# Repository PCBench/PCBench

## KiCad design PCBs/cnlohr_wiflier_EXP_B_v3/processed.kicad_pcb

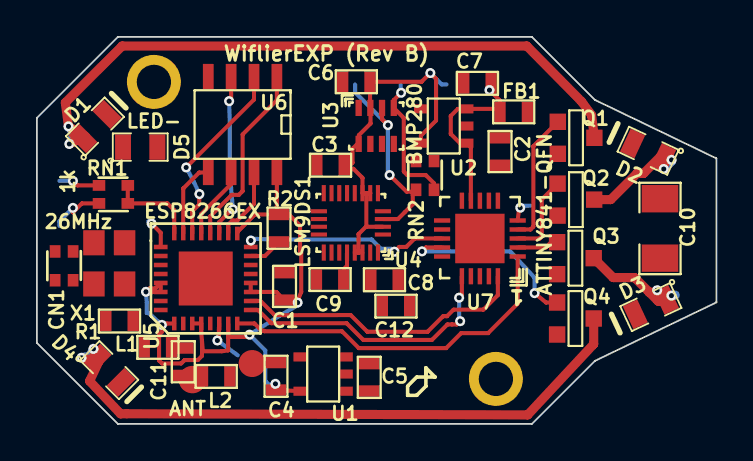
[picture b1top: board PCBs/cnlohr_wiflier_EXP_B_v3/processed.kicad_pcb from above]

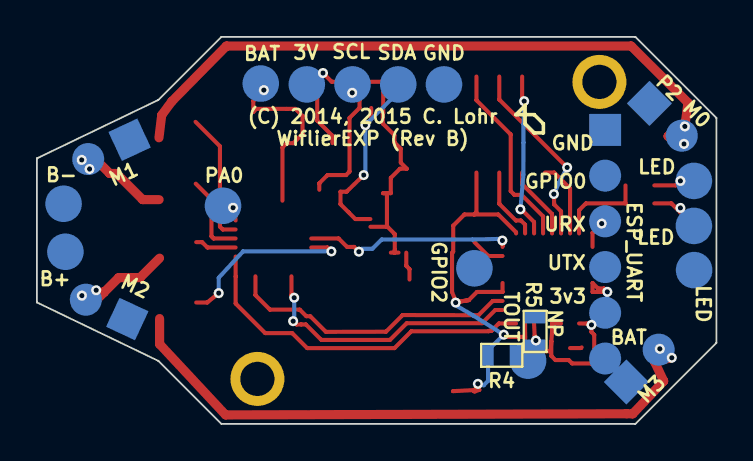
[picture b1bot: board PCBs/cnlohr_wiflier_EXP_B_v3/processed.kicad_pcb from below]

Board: 2 copper layers, 37.8 x 21.5 mm, 61 parts (20 on the bottom side), 28 nets.

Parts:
C1, C2, C3, C5: 10uF; SM0603
C4: 1uF; SM0603
C6, C8, C12: .1u; SM0603
C7: .1uF; SM0603
C9: 10nF; SM0603
C10: 100uF; SM1206
C11: 5.6pF; SM0603
CN1: 10p; NETWORK0606
D1, D2, D3, D4: 20V_500mA; SM0805
D5: LED-; SM0805
FB1: -; SM0603
L1, L2: NP; SM0603
P1: GPIO2; .1SMTPIN
P2: M0; SMT_1x2
P3: M1; SMT_1x2
P4: M2; SMT_1x2
P5: M3; SMT_1x2
P6, P19: ANT; .1SMTPIN
P7, P8: HOLE-1.9MM
P9: SDA; .1SMTPIN
P10: SCL; .1SMTPIN
P11: 3V; .1SMTPIN
P12: GND; .1SMTPIN
P13, P14, P15: LED; .1SMTPIN
P16: BAT; .1SMTPIN
P17: TOUT; .1SMTPIN
P18: PA0; .1SMTPIN
P21: B+; .1SMTPIN
P24: B-; .1SMTPIN
P32: ESP_UART; SMT_1x6
Q1, Q2, Q3, Q4: 7A_20V; SOT23GDS
R1, R2, R4: 12k; SM0603
R5: NP; SM0603
RN1, RN2: 1k; NETWORK0606
U1: MCP1824/3.3; SOT23-5
U2: MCP1824/3.0; SOT23-5
U3: BMP280
U4: LSM9DS1; LGA-24B
U5: ESP8266EX; QFN32
U6: W25Q16DV; SO8E
U7: ATTINY841-QFN; QFN20
X1: 26MHz; XTAL4P

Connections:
+3.3V: C1.1, R2.2, R4.1, U1.5, U5.1, U5.3, U5.4, U5.7, U5.11, U5.12, U5.17, U5.29, U5.30, U6.8
+3.3VP: C6.1, P11.1, U2.5, U4.3, U4.7, U4.8, U4.22, U4.23
AVRMISO: U5.10, U7.20
AVRMOSI: U5.9, U7.16
AVRRST: U5.16, U7.13
AVRSCK: U5.8, U7.1
GP5: RN1.1, RN1.3, U5.24
GPIO0: R2.1, U5.15
MTR0: Q1.G, U7.4
MTR1: Q2.G, U7.3
MTR2: Q3.G, U7.2
MTR3: Q4.G, U7.14
unnamed: P18.1, U7.5
unnamed: P13.1, RN1.2
unnamed: C9.2, U4.21
unnamed: C11.1, L1.1
unnamed: P14.1, RN1.4
unnamed: U5.20, U6.1
unnamed: U5.21, U6.6
unnamed: U5.22, U6.2
unnamed: U5.23, U6.5
unnamed: U5.19, U6.3
unnamed: U5.18, U6.7
SCL: P10.1, RN2.3, U3.4
SDA: P9.1, U3.3, U4.4
TOUT: R4.2, U5.6
URX: P32.3, U5.25
VAA: FB1.1, P16.1, U2.1, U2.3, U7.9

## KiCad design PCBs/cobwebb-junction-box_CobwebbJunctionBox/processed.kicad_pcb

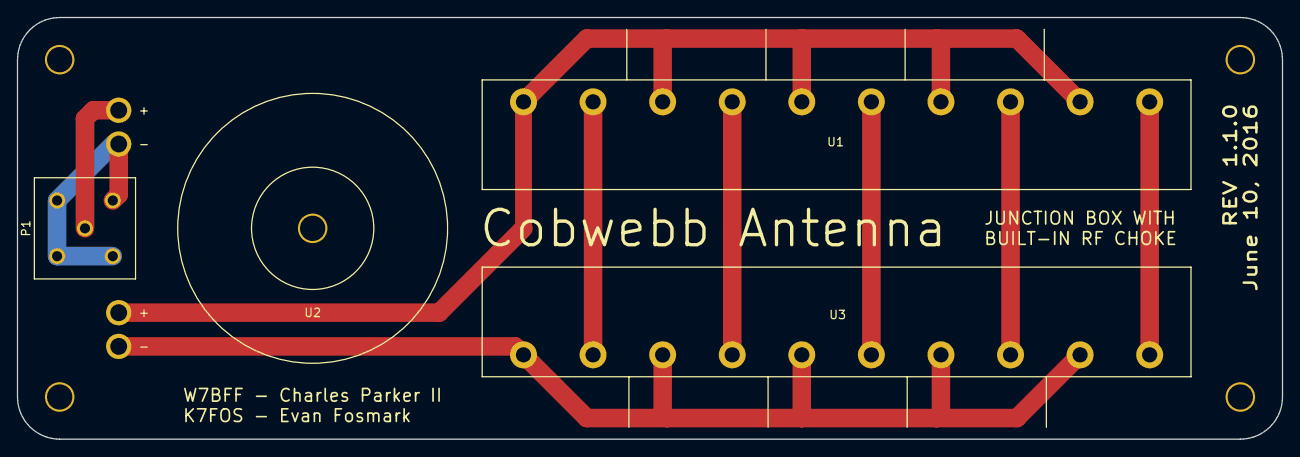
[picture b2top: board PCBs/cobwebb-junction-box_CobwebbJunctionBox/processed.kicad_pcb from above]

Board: 2 copper layers, 150.0 x 50.0 mm, 4 parts (0 on the bottom side), 9 nets.

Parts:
P1: BNC; BNC_Connector
U1, U3: Terminal_Block_10_Pin
U2: RF_Choke; RF_Choke_T106-2

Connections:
unnamed: P1.1, U2.2
unnamed: P1.2, U2.1
unnamed: U1.1, U3.10
unnamed: U1.3, U3.8
unnamed: U1.5, U3.6
unnamed: U1.7, U3.4
unnamed: U1.9, U3.2
unnamed: U1.2, U1.4, U1.6, U1.8, U1.10, U2.3
unnamed: U2.4, U3.1, U3.3, U3.5, U3.7, U3.9

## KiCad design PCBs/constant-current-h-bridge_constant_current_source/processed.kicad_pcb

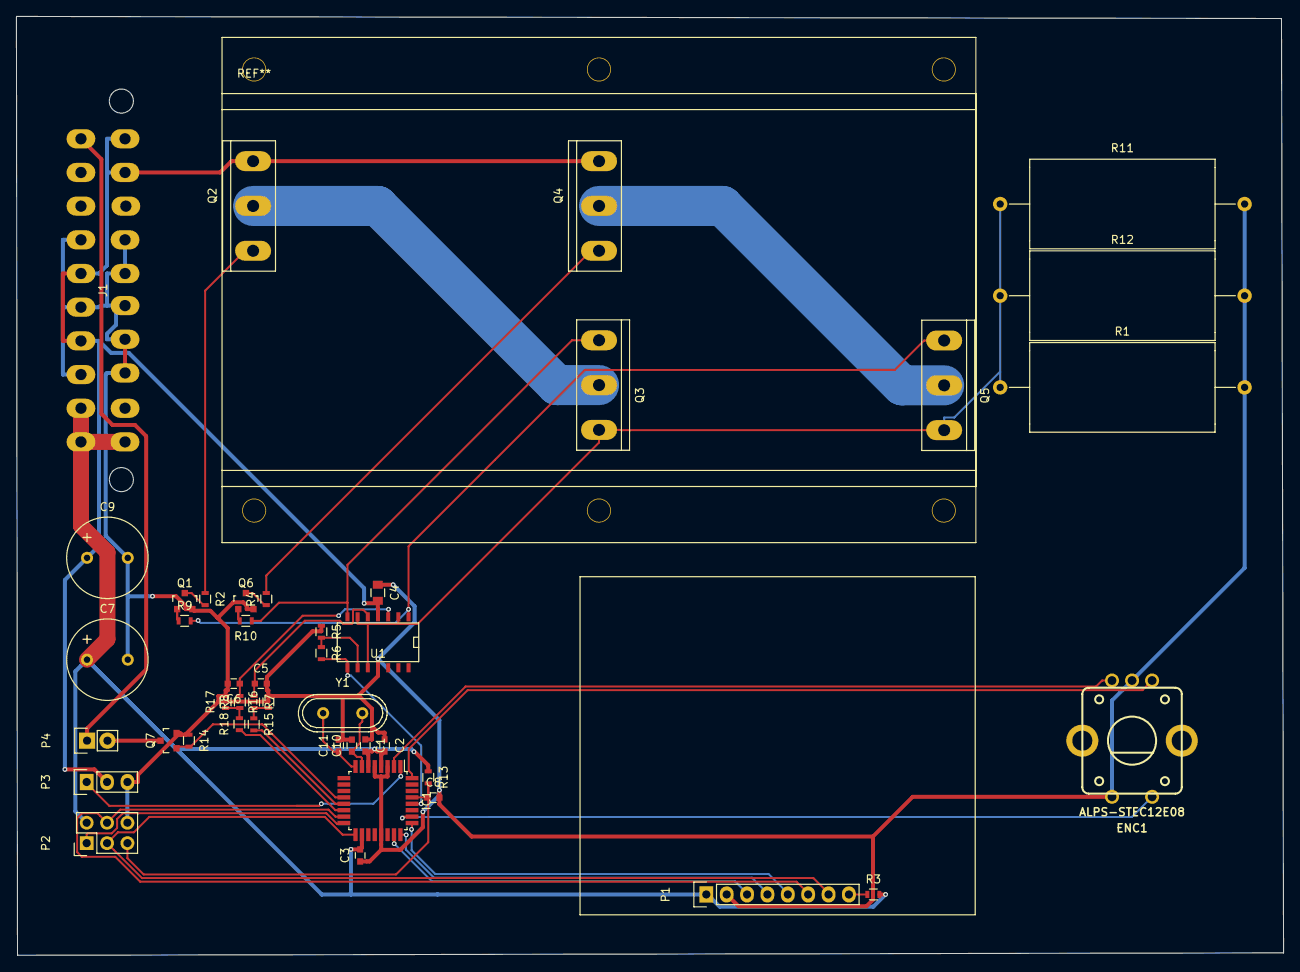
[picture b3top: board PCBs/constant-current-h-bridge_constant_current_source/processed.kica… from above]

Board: 2 copper layers, 158.0 x 117.1 mm, 45 parts (0 on the bottom side), 39 nets.

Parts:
C1, C2, C3: 100n; C_0603
C4: C; C_0805
C5, C6: 47n; C_0603
C7, C9: CP; Elko_vert_20x10mm_RM5
C8: C; C_0603
C10, C11: 22p; C_0603
ENC1: ALPS-STEC12E08
IC1: ATMEGA328P-A; TQFP-32_7x7mm_Pitch0.8mm
J1: ATX20; Molex_minifit_jr_5566_39-29-9203_20pin
P1: Nokia5110_Display
P2: CONN_02X03; Pin_Header_Straight_2x03
P3: CONN_01X03; Pin_Header_Straight_1x03
P4: CONN_01X02; Pin_Header_Straight_1x02
Q1, Q6: BC847; SOT-23
Q2, Q4: BD250; TO-247_Vertical_Neutral123
Q3, Q5: BD249; TO-247_Vertical_Neutral123
Q7: IRLML6244; SOT-23
R1, R11, R12: 0R1; Resistor_Ceramic_Horizontal_L23mm-W9mm-H9mm-p30mm
R2, R4: 1k5; R_0603
R3: 220; R_0603
R5, R9, R10, R14: 10k; R_0603
R6: 12k; R_0603
R7, R8: 100; R_0603
R13: R; R_0603
R15, R18: 180; R_0603
R16, R17: 150; R_0603
U1: LM324; SOIC-14_N
Y1: Crystal; Crystal_HC49-U_Vertical

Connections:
+3V3: C1.2, C2.2, C3.2, C7.1, IC1.4, IC1.6, IC1.18, J1.1, J1.2, J1.11, P1.1, P2.2, R3.2, R13.1
+5V: C4.2, C9.1, J1.4, J1.6, J1.19, J1.20, P3.2, Q2.3, Q4.3, U1.4
+12V: J1.10, P4.1
/MISO: IC1.16, P2.1
/MOSI: IC1.15, P1.6, P2.4
/RESET: C8.1, IC1.29, P2.5, R13.2
/SCK: IC1.17, P1.7, P2.3
/XTAL1: C10.1, IC1.7, Y1.2
/XTAL2: C11.1, IC1.8, Y1.1
/lcd_dc: IC1.25, P1.5
/lcd_rst: IC1.24, P1.4
/lcd_sce: IC1.23, P1.3
/load_1: Q2.2, Q3.2
/load_2: Q4.2, Q5.2
/mcu_adc: IC1.28, R6.2, U1.8
/mcu_airpump: IC1.12, Q7.1, R14.2
/opa_neg: Q5.1, R9.2, U1.1
/opa_pos: Q3.1, R10.1, U1.7
/pwm_neg: IC1.14, R18.1
/pwm_pos: IC1.13, R15.2
/rot_enc1: ENC1.A, IC1.32
/rot_enc2: ENC1.B, IC1.2
/rot_sw: ENC1.SW1, IC1.26
/servo_pwm: IC1.1, P3.1
GND: C1.1, C2.1, C3.1, C4.1, C5.2, C6.2, C7.2, C8.2, C9.2, C10.2, C11.2, ENC1.C, ENC1.SW2, IC1.3, IC1.5, IC1.21, J1.3, J1.5, J1.7, J1.13, J1.14, J1.15, J1.16, J1.17, P1.2, P2.6, P3.3, Q1.2, Q6.2, Q7.2, R1.2, R5.1, R11.2, R12.2, R14.1, R16.2, R17.2, U1.11
unnamed: C5.1, R7.1, U1.5
unnamed: C6.1, R8.2, U1.3
unnamed: P1.8, R3.1
unnamed: P4.2, Q7.3
unnamed: Q1.1, R9.1
unnamed: Q1.3, R2.2
unnamed: Q2.1, R2.1
unnamed: Q3.3, Q5.3, R1.1, R11.1, R12.1, U1.2, U1.6, U1.10
unnamed: Q4.1, R4.2
unnamed: Q6.1, R10.2
unnamed: Q6.3, R4.1
unnamed: R5.2, R6.1, U1.9
unnamed: R7.2, R15.1, R16.1
unnamed: R8.1, R17.1, R18.2

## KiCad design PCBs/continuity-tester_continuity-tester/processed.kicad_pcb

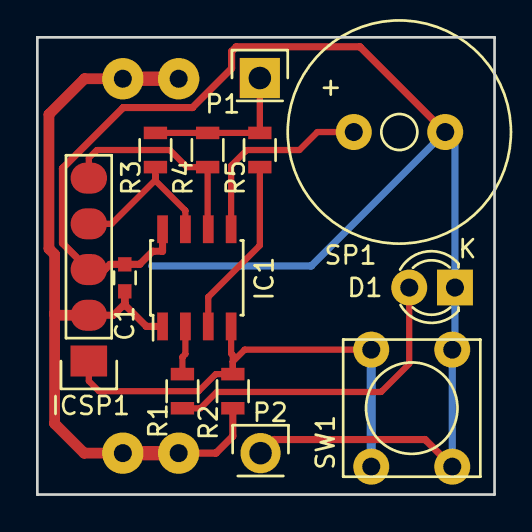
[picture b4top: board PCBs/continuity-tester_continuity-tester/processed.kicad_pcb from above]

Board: 2 copper layers, 25.4 x 25.4 mm, 14 parts (1 on the bottom side), 10 nets.

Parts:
BT1: CR2032; BAT-HLD-001-THM-OTL
C1: 100n; C_0603
D1: LED; LED-3MM
IC1: PIC12LF1571-I/SN; SOIC-8_3.9x4.9mm_Pitch1.27mm
ICSP1: CONN_01X05; Pin_Header_Straight_1x05
P1, P2: CONN_01X01; Pin_Header_Straight_1x01
R1: 4K7; R_0805
R2, R3, R4: 22k; R_0805
R5: 4k7; R_0805
SP1: SPEAKER; Buzzer_12x9.5RM7.6
SW1: SW_PUSH; SW_PUSH_SMALL

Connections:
unnamed: BT1.1, C1.1, IC1.1, ICSP1.2, R2.2
unnamed: BT1.2, C1.2, D1.1, IC1.8, ICSP1.3, P2.1, SP1.2, SW1.1
unnamed: D1.2, R1.1
unnamed: IC1.2, R1.2
unnamed: IC1.3, R5.2
unnamed: IC1.4, ICSP1.1, R2.1, SW1.2
unnamed: IC1.5, SP1.1
unnamed: IC1.6, ICSP1.5, R4.2
unnamed: IC1.7, ICSP1.4, R3.2
unnamed: P1.1, R3.1, R4.1, R5.1

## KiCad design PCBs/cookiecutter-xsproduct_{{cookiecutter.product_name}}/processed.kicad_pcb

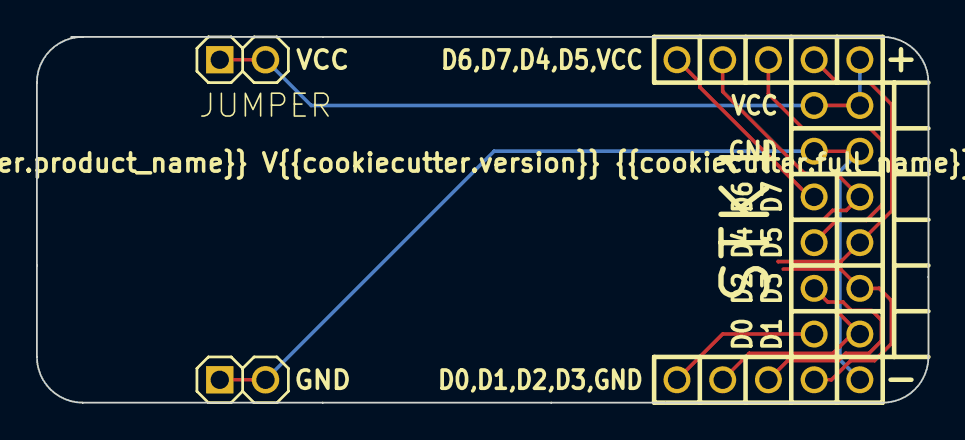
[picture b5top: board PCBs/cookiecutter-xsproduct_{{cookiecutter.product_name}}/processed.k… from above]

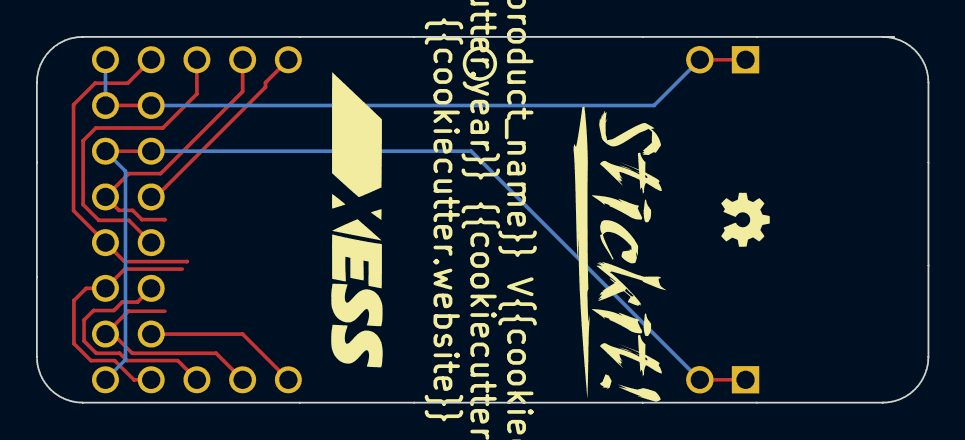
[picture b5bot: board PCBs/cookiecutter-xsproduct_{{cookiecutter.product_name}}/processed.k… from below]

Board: 2 copper layers, 49.5 x 20.3 mm, 6 parts (3 on the bottom side), 2 nets.

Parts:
A: B; oshw_logo_3mm
JP1, JP2: JUMPER; HDR_1x2
Noname_1: xess_logo_16mm
Noname_2: stickit_logo_16mm
STK1: STICKIT2_HDR

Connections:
GND: JP1.1, JP1.2, STK1.GND
VCC: JP2.1, JP2.2, STK1.VCC

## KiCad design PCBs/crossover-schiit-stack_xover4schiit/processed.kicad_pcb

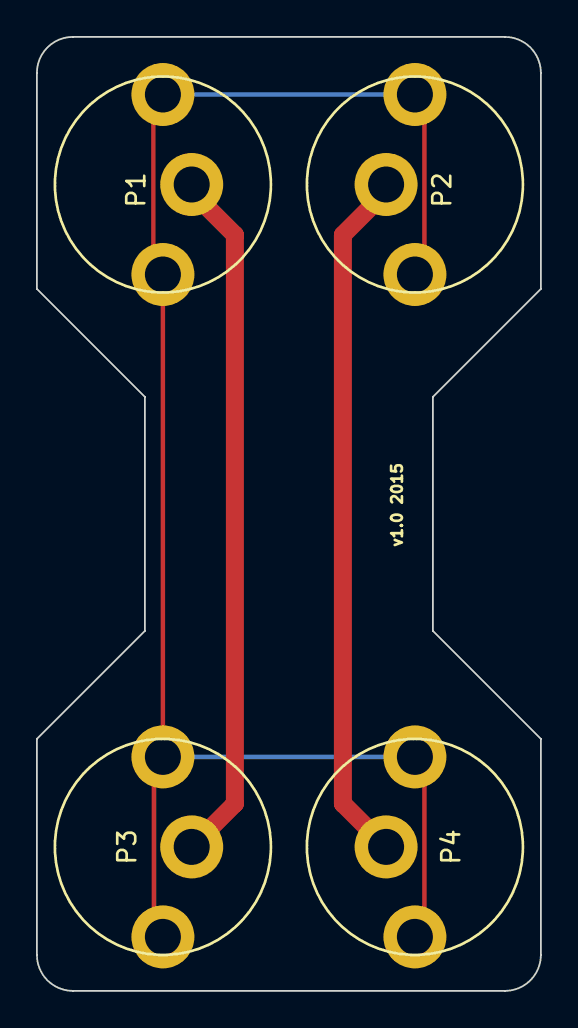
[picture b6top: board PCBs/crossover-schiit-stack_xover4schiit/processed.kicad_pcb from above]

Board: 2 copper layers, 28.0 x 53.0 mm, 4 parts (0 on the bottom side), 3 nets.

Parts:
P1, P2, P3, P4: bnc_pcb

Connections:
/A: P1.1, P3.1
/B: P2.1, P4.1
GND: P1.2, P2.2, P3.2, P4.2

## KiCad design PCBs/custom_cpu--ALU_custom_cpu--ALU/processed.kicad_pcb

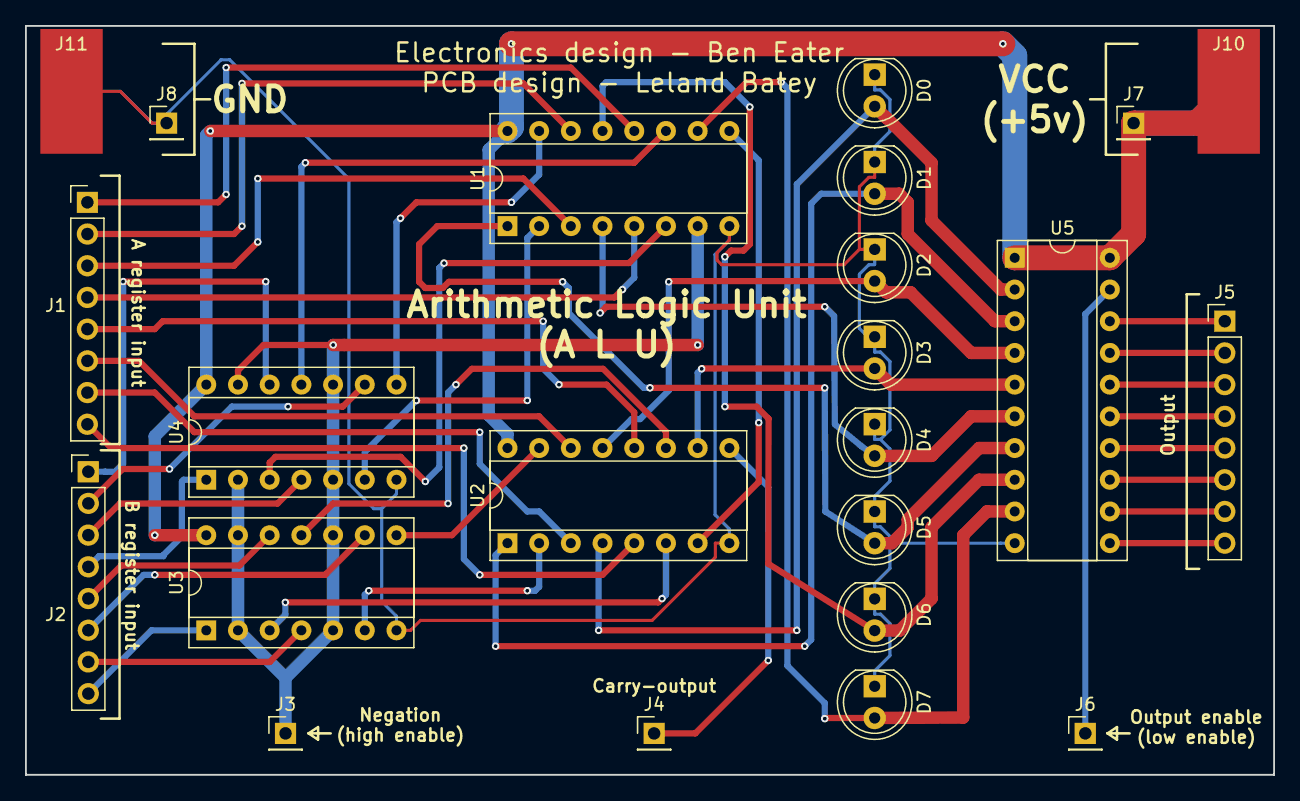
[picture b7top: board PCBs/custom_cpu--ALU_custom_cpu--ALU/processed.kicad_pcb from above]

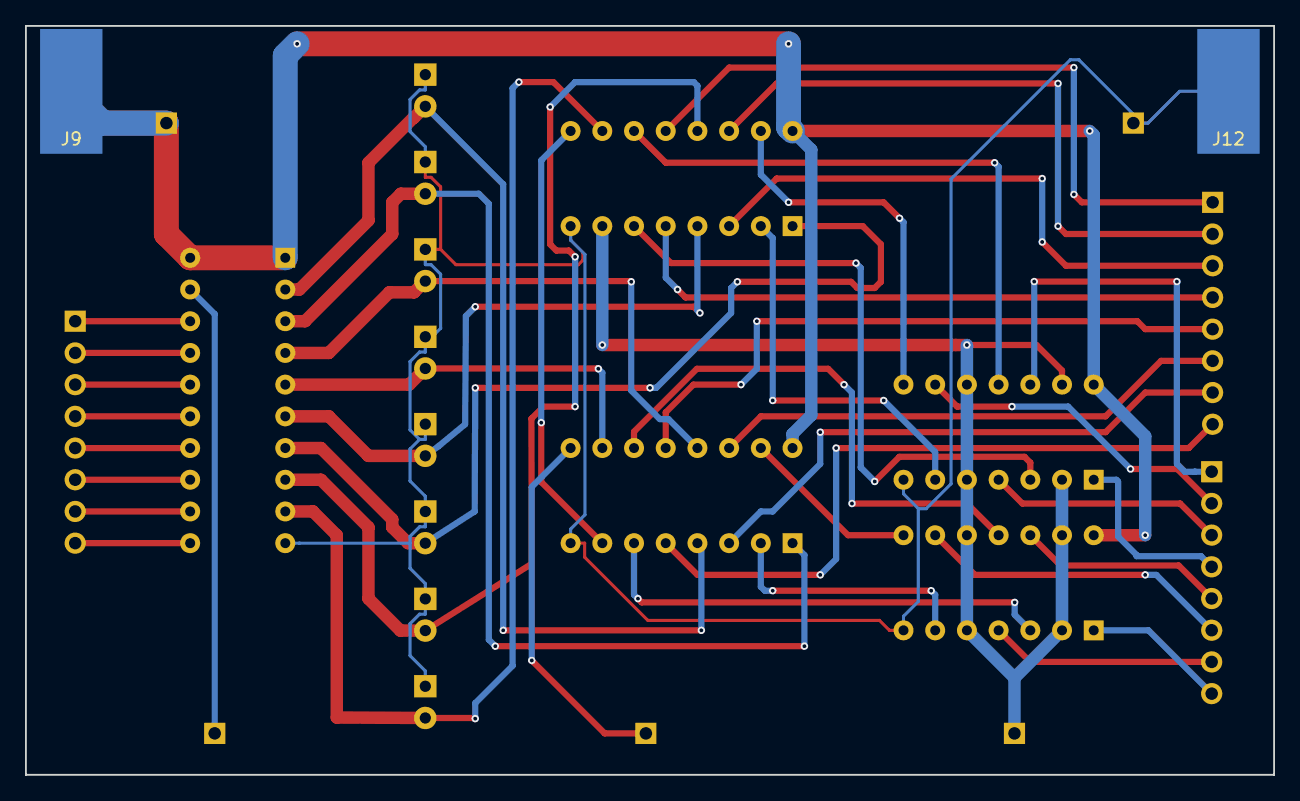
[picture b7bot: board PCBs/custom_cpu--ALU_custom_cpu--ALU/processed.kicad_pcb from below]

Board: 2 copper layers, 100.0 x 60.0 mm, 25 parts (2 on the bottom side), 46 nets.

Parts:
D0, D1, D2, D3, D4, D5, D6, D7: LED; LED_D5.0mm
J1, J2, J5: CONN_01X08; Pin_Header_Straight_1x08_Pitch2.54mm
J3, J4, J6, J7, J8: CONN_01X01; Pin_Header_Straight_1x01_Pitch2.54mm
J9, J10, J11, J12: CONN_01X01; SolderWirePad_single_SMD_5x10mm
U1, U2: 74LS283; DIP-16_W7.62mm_Socket
U3, U4: 74LS86; DIP-14_W7.62mm_Socket
U5: 74LS245; DIP-20_W7.62mm_Socket

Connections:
GND: D0.1, D1.1, D2.1, D3.1, D4.1, D5.1, D6.1, D7.1, J8.1, J11.1, J12.1, U1.8, U2.8, U3.7, U4.7, U5.10
unnamed: D0.2, U2.4, U5.2
unnamed: D1.2, U2.1, U5.3
unnamed: D2.2, U2.13, U5.4
unnamed: D3.2, U2.10, U5.5
unnamed: D4.2, U1.4, U5.6
unnamed: D5.2, U1.1, U5.7
unnamed: D6.2, U1.13, U5.8
unnamed: D7.2, U1.10, U5.9
unnamed: J1.1, U1.12
unnamed: J1.2, U1.14
unnamed: J1.3, U1.3
unnamed: J1.4, U1.5
unnamed: J1.5, U2.12
unnamed: J1.6, U2.14
unnamed: J1.7, U2.3
unnamed: J1.8, U2.5
unnamed: J2.1, U4.12
unnamed: J2.2, U4.9
unnamed: J2.3, U4.4
unnamed: J2.4, U4.1
unnamed: J2.5, U3.12
unnamed: J2.6, U3.9
unnamed: J2.7, U3.4
unnamed: J2.8, U3.1
unnamed: J3.1, U1.7, U3.2, U3.5, U3.10, U3.13, U4.2, U4.5, U4.10, U4.13
unnamed: J4.1, U2.9
unnamed: J5.1, U5.18
unnamed: J5.2, U5.17
unnamed: J5.3, U5.16
unnamed: J5.4, U5.15
unnamed: J5.5, U5.14
unnamed: J5.6, U5.13
unnamed: J5.7, U5.12
unnamed: J5.8, U5.11
unnamed: J6.1, U5.19
unnamed: U1.2, U4.6
unnamed: U1.6, U4.3
unnamed: U1.9, U2.7
unnamed: U1.11, U4.11
unnamed: U1.15, U4.8
unnamed: U2.2, U3.6
unnamed: U2.6, U3.3
unnamed: U2.11, U3.11
unnamed: U2.15, U3.8
VCC: J7.1, J9.1, J10.1, U1.16, U2.16, U3.14, U4.14, U5.1, U5.20

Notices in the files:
PCBs/cnlohr_wiflier_EXP_B_v3/processed.kicad_pcb:
Copyright 2015 < Charles Lohr
(C) 2014, 2015 C. Lohr
PCBs/continuity-tester_continuity-tester/processed.kicad_pcb:
©2015
